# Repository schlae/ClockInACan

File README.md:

# Clock In A Can
## Customizable can and half-can style crystal oscillators

Have you noticed that it is getting harder and harder to find through-hole
oscillators in the metal can or half-can packages? The selection has been
shrinking as manufacturers discontinue entire legacy product lines.

Fortunately, there is a solution! The ClockInACan is a small circuit board
that is the same size as the oscillator and duplicates the same function
exactly. Just provide your own crystal of the desired frequency or a multiple
of the desired frequency, and set the three solder jumpers to select the
divide ratio.

Features include

* Wide +2V to +5.5V power supply range
* Logic-level enable pin with internal pullup
* CMOS-compatible output
* Selectable divide ratio of 1, 1/2, 1/4, 1/8, 1/16, and 1/32
* Crystal footprint fits through hole and many surface mount crystals
* Pins are breadboard compatible, and also fit in DIP sockets
* Pins have labels underneath the PCB for your convenience

[Here is the schematic](https://github.com/schlae/ClockInACan/blob/master/ClockInACan.pdf).

Fab files can be found here:

* [ClockInACan fab files](https://github.com/schlae/ClockInACan/blob/master/fab/ClockInACanFab.zip)
* [ClockInAHalfCan fab files](https://github.com/schlae/ClockInACan/blob/master/fab/ClockInAHalfCanFab.zip)

The basic bill of materials is below.

| Q | Designator | Description     | Mouser Part Number   |
| - | ---------- | --------------- | -------------------- |
| 1 | U1         | Oscillator IC   | 513-NJU6311RB2-TE1   |
| 1 | C1         | 0.1uF capacitor | 603-CC603KRX7R9BB104 |
| 0 | C2, C3     | Optional load caps |                   |
| 0 | R1, R2, R3 | Divider jumpers |                      |
| 1 | R4         | 0 ohm solder jumper |                  |
| 1 | Y1         | Crystal         |                      |
| 4 | J1, J7, J8, J14 | PCB pins   | 575-0542000150000    |

Board dimensions below. Order the board in whatever cool colors you like!

* ClockInACan: 0.8 x 0.5 inches
* ClockInAHalfCan: 0.5 x 0.5 inches

## Assembly Notes

I've found it easiest to install the pins *before* soldering any components
on the board. Make a jig out of a block of wood, like this:

Then put the ClockInACan board on top, drop the four pins in place, and place
the whole thing into a small press or a bench vise, like this:

Apply enough pressure to push the pins into place, but no more.

Solder in C1 first, then U1 and R4. Set the R1, R2, and R3 jumpers to your
desired oscillator divider setting as follows:

| R1    | R2    | R3    | Setting |
| ----- | ----- | ----- | ------- |
| Open  | Open  | Open  | 1       |
| Short | Open  | Open  | /2      |
| Open  | Short | Open  | /4      |
| Short | Short | Open  | /8      |
| Open  | Open  | Short | /16     |
| Short | Open  | Short | /32     |

For your convenience, this table is reproduced on the bottom of the
ClockInACan PCB (although the ClockInAHalfCan does not have it due to space
constraints).

Install Y1, taking care not to short any component leads on the metal case of
the crystal. You may want to add Kapton tape to insulate the board from the
crystal. Large HC49 crystals can be folded over to save vertical space.

## Advanced Topics
The NJU6311 includes built-in load caps so C2 and C3 are not necessary unless
you have a particularly picky crystal. Similarly, R4 can be 0 ohms, but with
some crystals you may need to increase the resistance to reduce the drive
current. For further information see the [NJU6311 datasheet](https://www.njr.com/electronic_device/products/NJU6311.html).

## License
This work is licensed under a Creative Commons Attribution-ShareAlike 4.0
International License. See [https://creativecommons.org/licenses/by-sa/4.0/](https://creativecommons.org/licenses/by-sa/4.0/).

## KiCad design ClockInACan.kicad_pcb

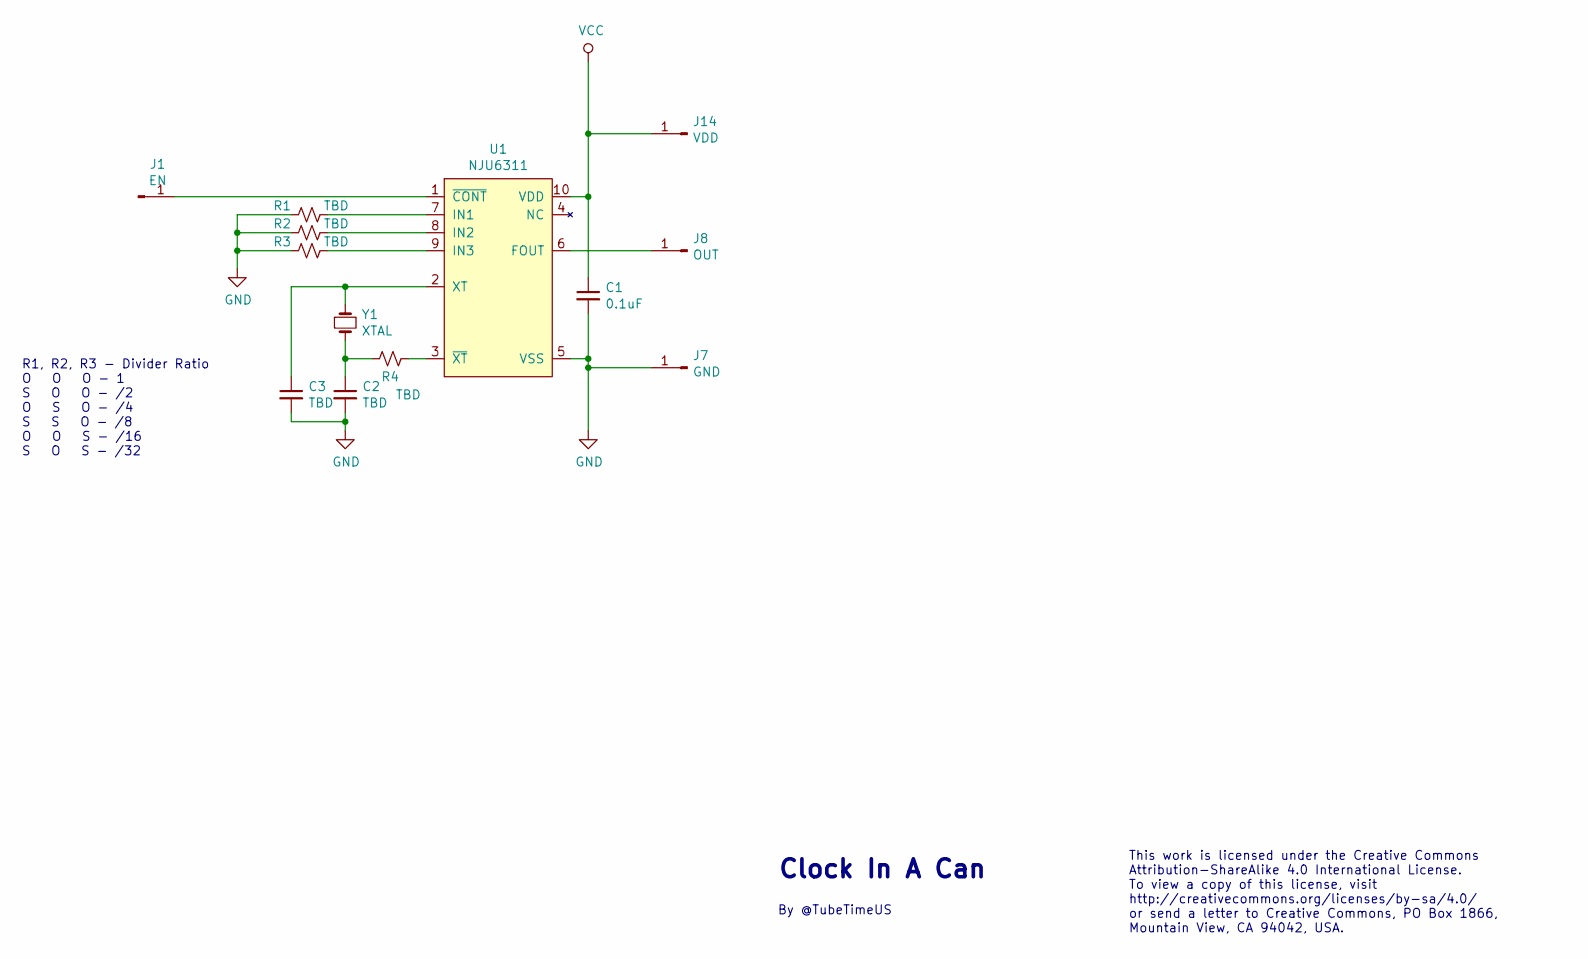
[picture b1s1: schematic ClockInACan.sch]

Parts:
C1: 0.1uF; CAPC1608X100
C2, C3: TBD; CAPC1608X100
J1: EN; MILL-MAX_0542-0-00-15-00-00-03-0; Mouser 575-0542000150000
J7: GND; MILL-MAX_0542-0-00-15-00-00-03-0; Mouser 575-0542000150000
J8: OUT; MILL-MAX_0542-0-00-15-00-00-03-0; Mouser 575-0542000150000
J14: VDD; MILL-MAX_0542-0-00-15-00-00-03-0; Mouser 575-0542000150000
R1, R2, R3: TBD; JMP1608
R4: TBD; RESC1608X55
U1: NJU6311; SSOP50P400X100-10; Mouser 513-NJU6311RB2-TE1
Y1: XTAL; XTAL500X320_HYBRID

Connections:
GND: C1.2, C2.2, C3.2, J7.1, R1.2, R2.2, R3.2, U1.5 (VSS)
unnamed: C2.1, R4.2, Y1.2
unnamed: C3.1, U1.2 (XT), Y1.1
unnamed: J1.1, U1.1 (~CONT)
unnamed: J8.1, U1.6 (FOUT)
unnamed: R1.1, U1.7 (IN1)
unnamed: R2.1, U1.8 (IN2)
unnamed: R3.1, U1.9 (IN3)
unnamed: R4.1, U1.3 (~XT)
VCC: C1.1, J14.1, U1.10 (VDD)

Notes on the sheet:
R1, R2, R3 - Divider Ratio O O O - 1 S O O - /2 O S O - /4 S S O - /8 O O S - /16 S O S - /32
By @TubeTimeUS
Clock In A Can
This work is licensed under the Creative Commons Attribution-ShareAlike 4.0 International License. To view a copy of this license, visit http://creativecommons.org/licenses/by-sa/4.0/ or send a letter to Creative Commons, PO Box 1866, Mountain View, CA 94042, USA.

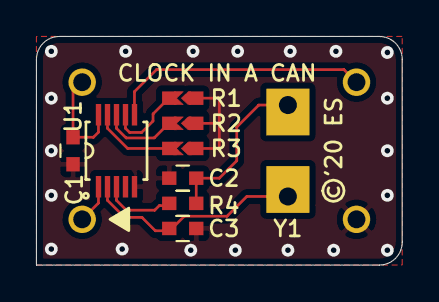
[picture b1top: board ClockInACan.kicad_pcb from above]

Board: 2 copper layers, 20.3 x 12.7 mm, 13 parts (0 on the bottom side), 10 nets.

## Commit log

2020-07-03 Initial empty commit.
2020-07-03 Initial commit.
2020-07-03 Fixes to README

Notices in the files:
ClockInACan.kicad_pcb:
Copyright (C) 2020 Eric Schlaepfer
©'20 ES
